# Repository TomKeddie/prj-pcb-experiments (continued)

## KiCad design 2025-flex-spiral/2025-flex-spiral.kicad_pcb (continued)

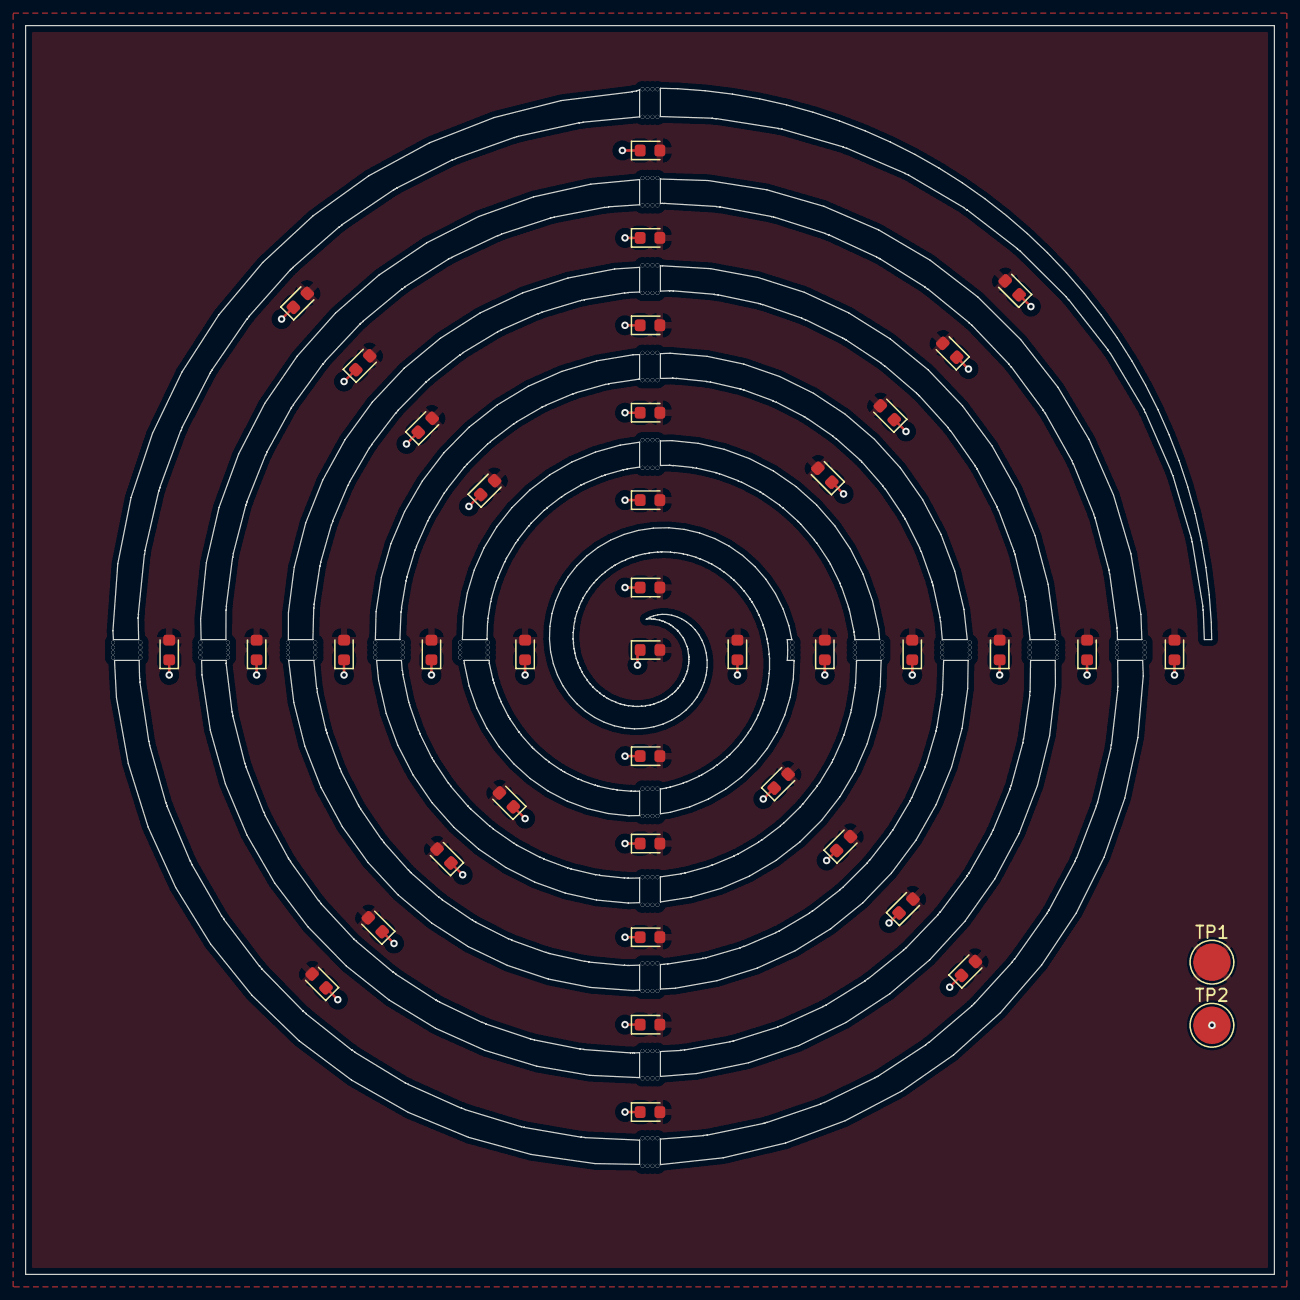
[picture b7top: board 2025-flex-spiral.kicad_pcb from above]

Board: 2 copper layers, 100.0 x 100.0 mm, 41 parts (0 on the bottom side), 2 nets.

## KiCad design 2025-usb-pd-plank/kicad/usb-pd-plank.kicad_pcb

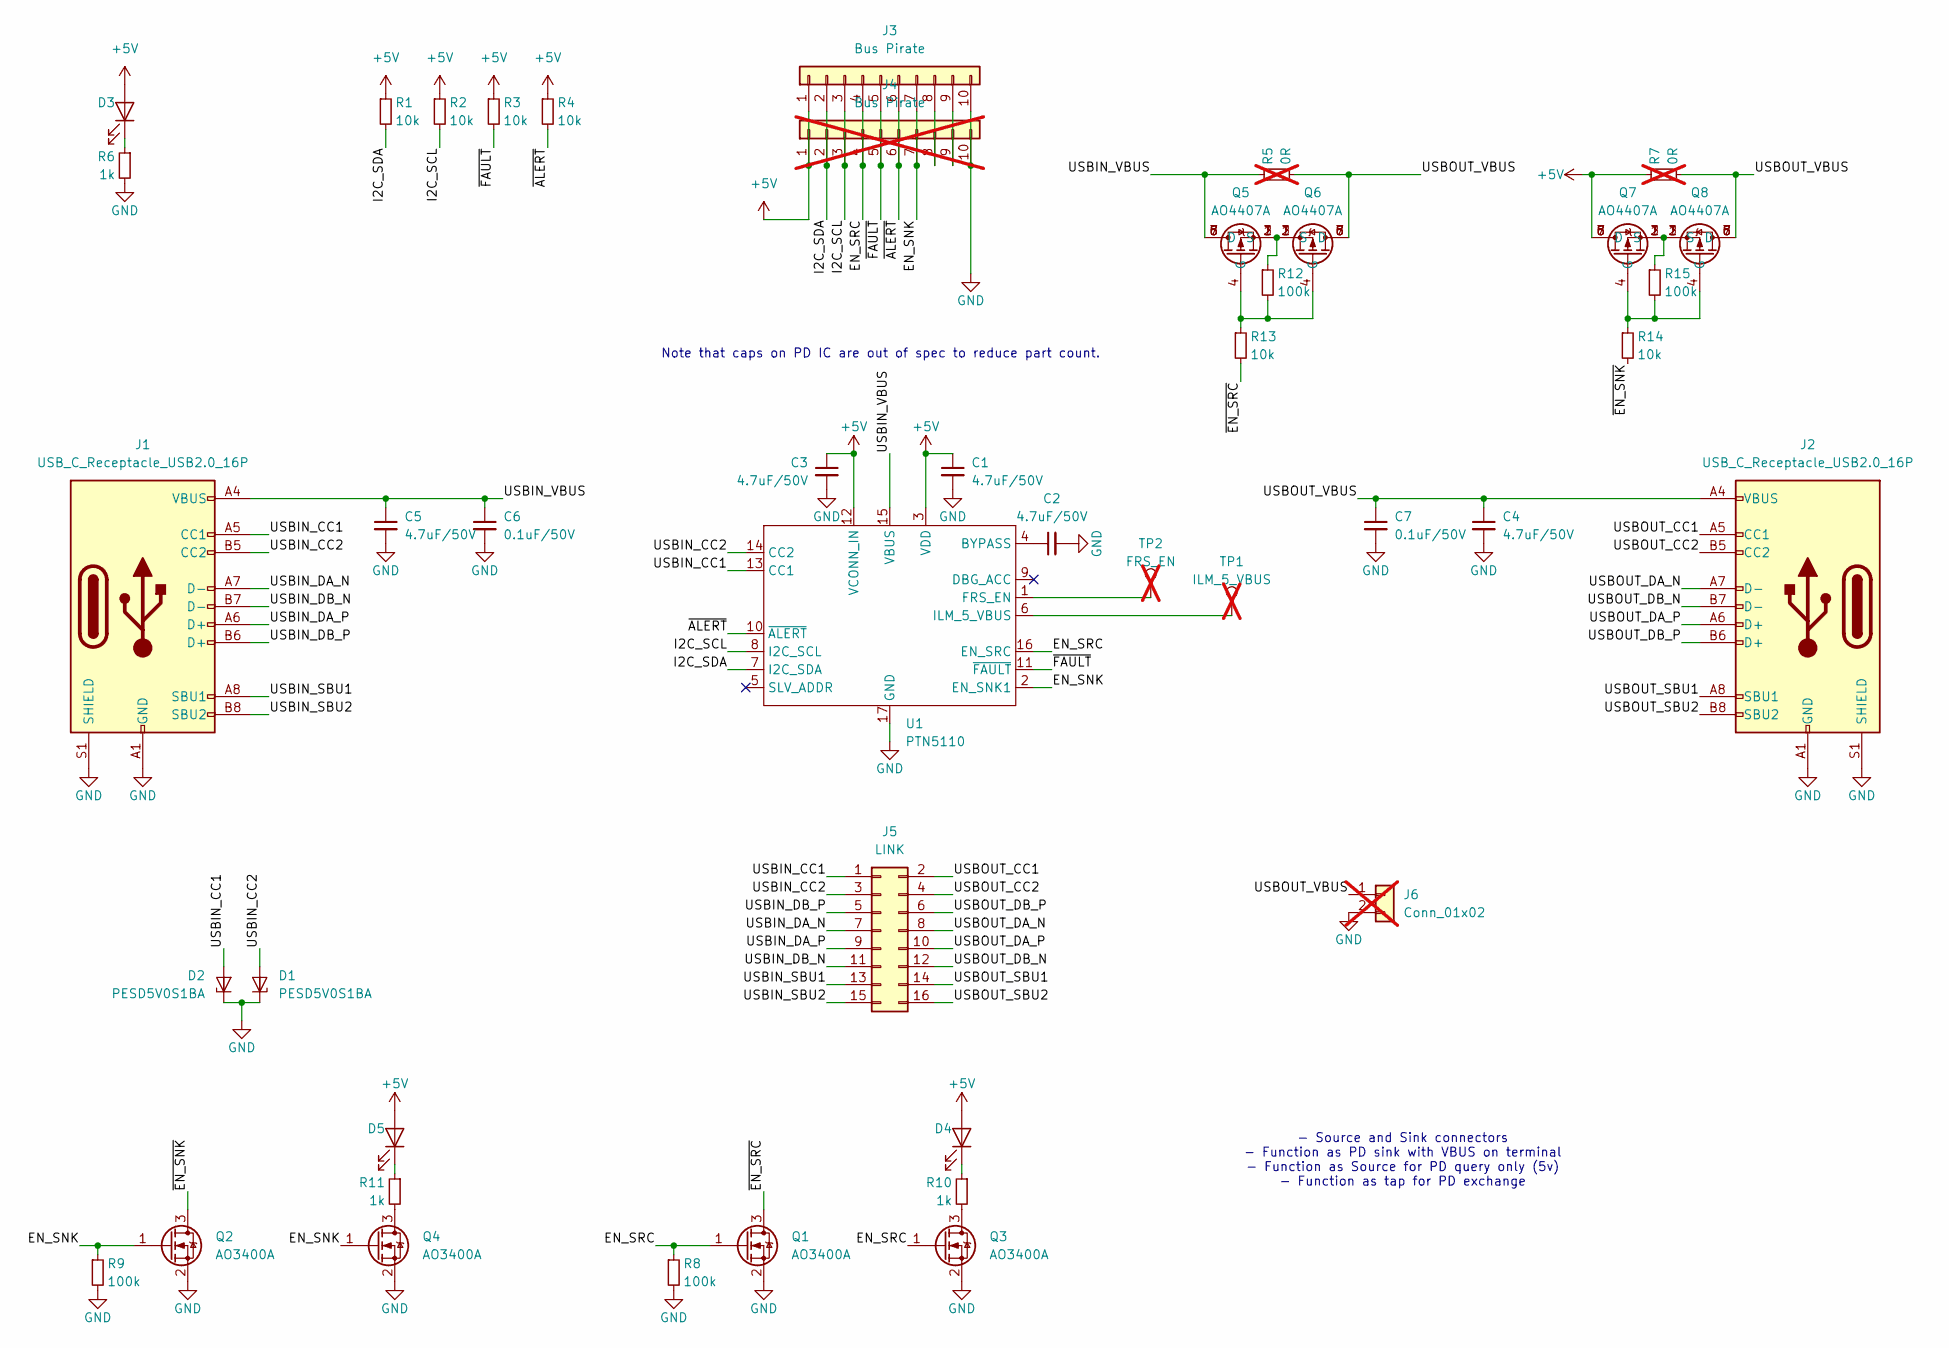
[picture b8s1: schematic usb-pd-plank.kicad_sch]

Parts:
C1, C2, C3, C4, C5: 4.7uF/50V; C_1206_3216Metric; LCSC C29823
C6, C7: 0.1uF/50V; C_1206_3216Metric; LCSC C24497
D1, D2: PESD5V0S1BA; D_SOD-323; LCSC C19224
D3, D4, D5: GREEN; LED_0805_2012Metric; LCSC C2297
J1, J2: USB_C_Receptacle_USB2.0_16P; USB_C_Receptacle_LCSC_C165948; LCSC C165948
J3: Bus Pirate; PinSocket_1x10_P2.54mm_Horizontal
J4: Bus Pirate; PinSocket_1x10_P2.54mm_Vertical; not fitted
J5: LINK; PinHeader_2x08_P2.54mm_Vertical
J6: Conn_01x02; JST_PH_S2B-PH-SM4-TB_1x02-1MP_P2.00mm_Horizontal; not fitted
Q1, Q2, Q3, Q4: AO3400A; SOT-23-GSD; LCSC C20917
Q5, Q6, Q7, Q8: AO4407A; SO-8_3.9x4.9mm_P1.27mm
R1, R2, R3, R4, R13, R14: 10k; R_0402_1005Metric; LCSC C25744
R5, R7: 0R; R_0402_1005Metric; LCSC C17168; not fitted
R6, R10, R11: 1k; R_0402_1005Metric; MFGPN 0402WGF1001TCE; LCSC C11702
R8, R9, R12, R15: 100k; R_0402_1005Metric; MFGPN 0402WGF1003TCE; LCSC C25741
TP1: ILM_5_VBUS; TestPoint_Pad_D1.5mm; not fitted
TP2: FRS_EN; TestPoint_Pad_D1.5mm; not fitted
U1: PTN5110; QFN-16_EP_2.6x2.6_Pitch0.4mm; LCSC C2674062

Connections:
+5V: C1.1, C3.1, D3.2 (A), D4.2 (A), D5.2 (A), J3.1, J4.1, Q7.5 (D), Q7.6 (D), Q7.7 (D), Q7.8 (D), R1.1, R2.1, R3.1, R4.1, R7.1, U1.3 (VDD), U1.12 (VCONN_IN)
/EN_SNK: J3.7, J4.7, Q2.1 (G), Q4.1 (G), R9.1, U1.2 (EN_SNK1)
/EN_SRC: J3.4, J4.4, Q1.1 (G), Q3.1 (G), R8.1, U1.16 (EN_SRC)
/I2C_SCL: J3.3, J4.3, R2.2, U1.8 (I2C_SCL)
/I2C_SDA: J3.2, J4.2, R1.2, U1.7 (I2C_SDA)
/USBIN_CC1: D2.2 (A), J1.A5 (CC1), J5.1, U1.13 (CC1)
/USBIN_CC2: D1.2 (A), J1.B5 (CC2), J5.3, U1.14 (CC2)
/USBIN_DA_N: J1.A7 (D-), J5.7
/USBIN_DA_P: J1.A6 (D+), J5.9
/USBIN_DB_N: J1.B7 (D-), J5.11
/USBIN_DB_P: J1.B6 (D+), J5.5
/USBIN_SBU1: J1.A8 (SBU1), J5.13
/USBIN_SBU2: J1.B8 (SBU2), J5.15
/USBIN_VBUS: C5.1, C6.1, J1.A4 (VBUS), J1.A9 (VBUS), J1.B4 (VBUS), J1.B9 (VBUS), Q5.5 (D), Q5.6 (D), Q5.7 (D), Q5.8 (D), R5.1, U1.15 (VBUS)
/USBOUT_CC1: J2.A5 (CC1), J5.2
/USBOUT_CC2: J2.B5 (CC2), J5.4
/USBOUT_DA_N: J2.A7 (D-), J5.8
/USBOUT_DA_P: J2.A6 (D+), J5.10
/USBOUT_DB_N: J2.B7 (D-), J5.12
/USBOUT_DB_P: J2.B6 (D+), J5.6
/USBOUT_SBU1: J2.A8 (SBU1), J5.14
/USBOUT_SBU2: J2.B8 (SBU2), J5.16
/USBOUT_VBUS: C4.1, C7.1, J2.A4 (VBUS), J2.A9 (VBUS), J2.B4 (VBUS), J2.B9 (VBUS), J6.1, Q6.5 (D), Q6.6 (D), Q6.7 (D), Q6.8 (D), Q8.5 (D), Q8.6 (D), Q8.7 (D), Q8.8 (D), R5.2, R7.2
/~ALERT: J3.6, J4.6, R4.2, U1.10 (~ALERT)
/~EN_SNK: Q2.3 (D), R14.2
/~EN_SRC: Q1.3 (D), R13.2
/~FAULT: J3.5, J4.5, R3.2, U1.11 (~FAULT)
GND: C1.2, C2.2, C3.2, C4.2, C5.2, C6.2, C7.2, D1.1 (K1), D2.1 (K1), J1.A1 (GND), J1.A12 (GND), J1.B1 (GND), J1.B12 (GND), J1.S1 (SHIELD), J2.A1 (GND), J2.A12 (GND), J2.B1 (GND), J2.B12 (GND), J2.S1 (SHIELD), J3.10, J4.10, J6.2, Q1.2 (S), Q2.2 (S), Q3.2 (S), Q4.2 (S), R6.2, R8.2, R9.2, U1.17 (GND)
unnamed: D3.1 (K), R6.1
unnamed: D4.1 (K), R10.1
unnamed: D5.1 (K), R11.1
unnamed: J3.8, J4.8
unnamed: J3.9, J4.9
unnamed: Q3.3 (D), R10.2
unnamed: Q4.3 (D), R11.2
unnamed: Q5.4 (G), Q6.4 (G), R12.2, R13.1
unnamed: Q5.1 (S), Q5.2 (S), Q5.3 (S), Q6.1 (S), Q6.2 (S), Q6.3 (S), R12.1
unnamed: Q7.4 (G), Q8.4 (G), R14.1, R15.2
unnamed: Q7.1 (S), Q7.2 (S), Q7.3 (S), Q8.1 (S), Q8.2 (S), Q8.3 (S), R15.1
unnamed: C2.1, U1.4 (BYPASS)
unnamed: TP2.1, U1.1 (FRS_EN)
unnamed: TP1.1, U1.6 (ILM_5_VBUS)

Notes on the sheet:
Note that caps on PD IC are out of spec to reduce part count.
- Source and Sink connectors - Function as PD sink with VBUS on terminal - Function as Source for PD query only (5v) - Function as tap for PD exchange

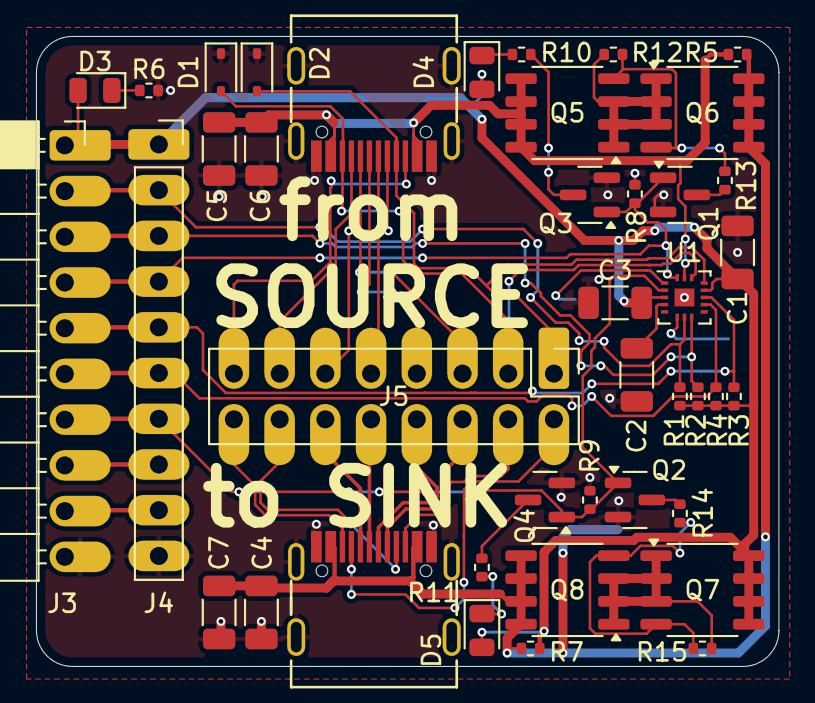
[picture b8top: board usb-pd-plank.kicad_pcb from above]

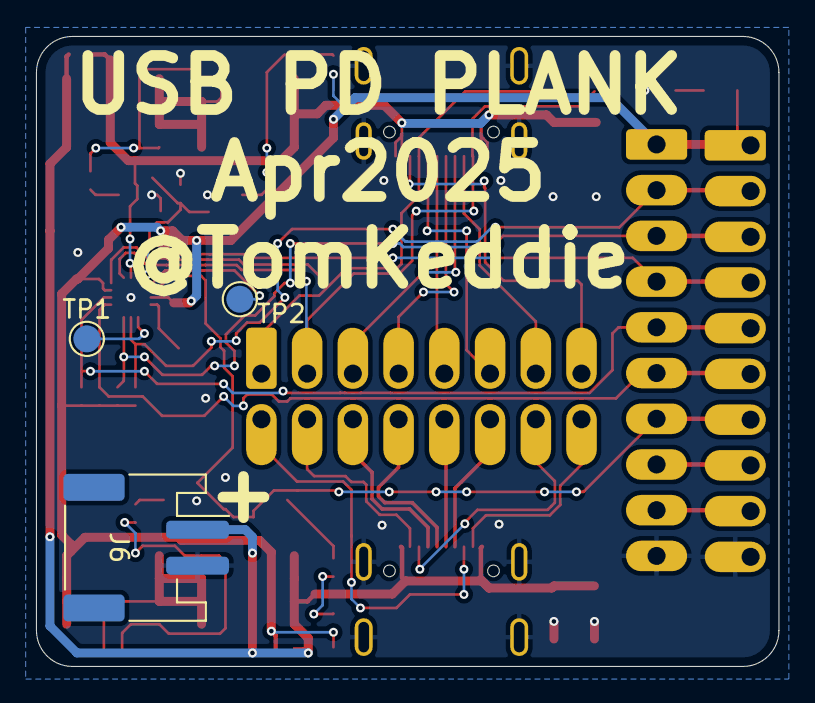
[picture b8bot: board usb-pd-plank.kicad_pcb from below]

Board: 2 copper layers, 41.2 x 35.0 mm, 44 parts (3 on the bottom side), 42 nets.

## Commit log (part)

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2019-01-28 Add led-through-fibreglass test board as submitted to oshpark
2019-08-24 Adding first pass at east van pcb
2019-08-24 Added east-van logo library elements - cu, mask and silk
2019-08-24 Updated east-vanm pcb - add leds - route tracks
2019-08-24 Add remaining east van image files
2019-08-24 East Van pcb as submitted
2019-08-28 Move east van cross to subdirectory
2019-08-28 Add east van arrow image experiments
2019-08-28 Add east van sao outline prototypes
2019-11-01 east-van/pendant-rear: new pcb, swap copper layers
2019-11-01 east-van/pendant-rear: flip silk and mask to create rear (with mirrored writing)
2019-11-01 Update tom-kicad libraries
2019-11-01 east-van: add gimp image.xcf with image portions on different layers
2019-11-01 east-van/pendant: add gerbers
2019-11-21 deutsche-bahn-sao: add scaled and edge images, dxf and footprints (scaled to 70%)
2019-11-21 deutsche-bahn-sao: artwork complete, needs LEDs and sao connector
2019-11-21 Update tom-kicad submodule
2019-11-22 deutsche-bahn: v1.0 as submitted
2019-11-22 mrfixit: add graphics
2019-11-22 mrfixit: add inkspace and dxf
2019-11-22 mrfixit: first pass at pcb
2019-11-22 mrfixit: add copper layers
2019-11-22 mrfixit: v1.0 as submitted, hasl copper outline with red mask internal + multimeter led
2019-11-22 east-van-arrow:add all images
2019-11-22 east-van-arrow: added scaled and filled images
2019-11-23 east-van-arrow: v1.0 as submitted
2019-11-23 east-van-arrow: v1.0 revised larger
2019-11-26 mr-fixit: v1.1 edge cuts changes as v1.0 failed audit
2019-11-26 mr-foxot: add v1.1 gerber zip
2019-11-27 glasgow-pmod: add v1.0
2019-11-29 edison-led-3x4-pmod: rev v1.0
2019-11-29 tom-kicad: added footprints for glasgow pmod adapter
2019-12-07 eat-van-arrow: v1.1 fix issues with back solder mask
2019-12-13 Added various pcb images
2020-01-29 hc245t-bypass: first pass
2020-02-02 hub75-pmod: feb 2020 added
2020-02-02 hc245t-bypass: create panel of two to account for oshpark min size
2020-02-29 hc245t-bypass: Feb 2020 version, increase spacing between boards
2020-02-29 hc245t-bypass: revert to Jan2018 version for flex pcb
2020-02-29 hc245t-bypass : flex version as submitted to oshpark for Feb 2020
2020-03-01 hc245t-bypass: Mar2020 rev with 4 instances
2020-03-01 hc245t-bypass.kicad_pcb: fix solder mask settings
2020-03-02 pi4-pcie-patch: no castellations
2020-03-02 pi4-pcie-patch: add castellations
2020-03-02 pi4-pcie-patch: mask pads on bottom layer
2020-04-09 hub75-pmod: fix issues with oval pads for hub75 connector
2020-04-10 Add covid mask images
2020-04-10 Update gitignore and tom-kicad anchor
2020-04-10 covid-mask: final dxf and jpeg
2020-04-11 covid-mask: add mask2 gerbers
2020-05-18 Glasgow LVDS-PMOD: May 2020 update, fixed mechanical issues
2020-05-24 glasgow-pmod : use relative paths for footprints
2020-05-24 glasgow pmod : fix library references
2020-05-26 glasgow-pmod: tuned J3 and J4 J3_J4_DP1.0/1.0 -> MEETS INTER-PAIR TOLERANCE 1.0000 mm (current delta 0.8724) /Z0 meets intra-pair tolerance 1.0000 mm (current delta 0.0000) /Z1 meets intra-pair toler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
2020-05-31 glasgow pmod: June 2020 release, fix length matching of pairs
2020-06-28 Glasgow lvds pmod - June 2020
2020-07-25 big-clive: add coaster and keytag pcbs
2020-07-25 big-clive: fix zip file naming
2020-08-06 usb3-loopback: new project
2020-08-09 usb-crossover: new pcb to cross HS tx & rx pairs for usb3<->pcie
2020-09-18 add multi-way-usb sep2020a as resent to jlcpcb
2020-09-19 multi-way-usb: fix drc errors related to keepout regions
2020-09-19 update tom-kicad anchor
2020-09-19 multi-way-usb: as submitted
2020-09-20 esp8266-iot: as submitted to jlcpcb
2020-09-29 sao-wall : as sent to jlcpcb Sep 2020
2020-09-29 Update modules
2020-10-10 Add 3rdparty-gerbers
2020-10-10 Submodule updates
2020-10-10 Moved sao-wall to git@github.com:TomKeddie/prj-sao-wall.git
2020-10-14 multi-way-usb: Changed footprint for inverted connectors
2020-10-20 Add p-bjt-spice: pnp spice simulation
2020-10-20 Add p-fet-spice: P channel fet simulation
2020-11-27 multi-way-usb: fix mechanical issues
2020-11-27 Add syzygy-serdes-breakout
2020-11-29 Add atmelice-swd-breakout
2020-11-29 multi-way-usb: move J8 to X2 to balance supplies, v1.2 ready for production
2020-12-08 2021-xmas-tree: add png for ornament
2020-12-10 Add 2021-xmas-tree pcb ornament
2020-12-11 2021-xmas-tree: Dec2020 release
2020-12-11 Add rgb-xmas-tree (need to solve current consumption)
2020-12-11 2021-xmas-tree-2020Dec: reduced to 100mm size to save $$
2020-12-11 atmelice-swd-breakout: Nov2020 release
2020-12-11 Add syzygy-stencil
2020-12-12 syzygy-serdes-breakout: fix missing ground pour on In1
2020-12-12 Add Iron Man gerbers
2020-12-12 peace-sign: add image
2020-12-13 peace-sign-sao: new design
2020-12-16 blue-pill-bmp: add 2.54mm SWD connector
2020-12-16 peace-sign: commit missing updates
2020-12-16 peace-sign-sao: change SAO connector back to 6 pin for stability
2020-12-17 atmelice-swd-breakout-switch: new design
2020-12-28 kicad-symbols-footprints-workshop: pcb workshop files
2021-01-04 Add power blower
2021-01-04 cleanup
2021-01-07 peace-sign-sao: add source image
2021-01-13 kindcalmsafe: new design
2021-01-13 kindcalmsafe: commit unsaved schematic changes
2021-01-15 snoopy-sao: new design
2021-01-15 snoopy-sao: fix silk
2021-01-15 kindcalmsafe: fix 1204 led package
2021-02-04 micromod-carrier: first commit before hub part # change
2021-02-19 esp8266-wiz550io: new design
2021-02-19 esp8266-wiz550io: add gerbers
2021-02-19 esp8266-wiz550io: switch GPIO2 and GPIO4
2021-02-26 atmelice-swd-breakout-switch: add AVR connector (2021Jan rev)
2021-02-26 nrf52dk-trace-pmod: flip data pin orientation to match pmod
2021-02-26 blue-pill-bmp: as submitted
2021-02-26 peace-sign-sao: as submitted
2021-02-26 kindcalmsafe: dxf export
2021-02-26 snoopy-sao/woodstock: first pass on woodstock
2021-02-26 micromod-carrier: progress commit
2021-02-26 esp8266-iot: add comments
2021-02-26 tom-kicad: update anchor
2021-02-26 kicad-symbols-footprints-workshop: add alias
2021-02-26 power-blower: as committed
2021-02-26 reinstate tom-kicad after conflict mess
2021-03-26 galep4-plcc-28: new design
2021-03-27 galep4-plcc-28: Mar2021 release
2021-04-17 esp8266-wiz550io: add kibot output for Feb2021 release
2021-04-19 ft4232h-breakout: Apr2021 release
2021-04-25 keypad-base: new design
2021-04-25 keypad-base: reduced to 6 keys, add mode change side buttons
2021-04-25 keypad-base: Apr2021 release
2021-04-25 keypad-frame: Apr2021 release of keypad frame
2021-04-25 keypad-base: fix silk, add missing edge cuts layer
2021-04-25 ft4232h-breakout: regenerate Apr2021 with edge cuts
2021-04-26 esp8266-wiz550io: regenerate Feb2021 gerbers with missing edge cuts fixed
2021-04-26 keypad-base/keypad-frame: change to M2 standoffs, Apr2021a release
2021-05-30 ft4232h-breakout: may release - change to SMTSO-M3 standoff
2021-05-30 keypad-frame: May2021 release, change to m3 holes, shrink keyswitch cutouts
2021-06-06 ft4232h-breakout: Jun2021 release, fix diameter of spacer
2021-06-06 ft4232h-breakout: Jun2021a release, add power led
2021-06-06 ft4232h-breakout: Jun2021b add silk to voltage selection
2021-06-06 keypad-base: Jun2021 - change standoff type
2021-12-26 micromod-pmod-function: adapter for micromod function to pmod
2022-01-22 keypad-prototype: moved to git@github.com:TomKeddie/prj-keypad-six.git
2022-01-22 usb-c-power-toggle: new design, as sent to Oshpark
2022-02-06 rc2014-compat-backplane: new design feb2022 rev
2022-02-06 rc2014-compat-backplane: remove extra drill files
2022-05-12 ft4232h-breakout: directory restructure to make way for v2.x
2022-05-12 ft4232h-breakout: add v2.x
2022-05-13 ft4232h-breakout: first pass at v3, pcb outline done
2022-05-14 ft4232h-breakout: v3 schematic complete and reviewed
2022-05-15 ft4232h-breakout: v3 at rc1
2022-05-15 ft4232h-breakout: v3.0 as submitted to jlcpcb for pcb run
2022-06-03 ft4232h-breakout: updates for v3.1
    - fixed mount hole sizes
    - fixed exterior dimensions
    - updated rev on silk
2022-12-02 ch348_octo_serial: 8 port usb serial adapter. Placed.
2022-12-03 ch348_octo_serial: fully routed, silk pending
2022-12-04 ch348_octo_serial: Dec2022 as submitted
2022-12-12 2022-xmas-ball: as submitted to jlcpcb/elecrow
2022-12-15 ch348_octo_serial: add pin 1 marking
2022-12-25 covid-dude: SAO based on teachmepcb image, Dec2022 release
2022-12-25 covid-dude: fix date in filename
2023-01-22 ch348_octo_serial_minim: compact ch348 board, wip
2023-01-23 ch348_octo_serial_minim: jan2023 rev ready for production
2023-01-23 ch348_octo_serial_minim: add cover plate pcb
2023-01-23 ch348_octo_serial_minim: move plate to subdir, add cts/rts link, Jan2023a
2023-01-25 covid-dude: add JLCJLC text
2023-03-31 skull-roses: skull and roses game with pcbs
2023-03-31 skull-roses: update Makefile to be generic
2023-03-31 roses: added step file generation
2023-04-20 esp8266-plugpack - new design
2023-04-22 esp8266-plugpack: placed and routed
2023-04-22 esp8266-plugpack: regenerate mfg output
2023-04-24 esp8266-plugpack: Apr2023 release
2023-05-04 atmelice-swd-breakout-switch: fix ground issue, May2023 release
2023-09-13 baggage-label: new design
2023-09-19 webcam-shim: new design
2023-09-23 baggage-label-small: new design
2023-11-01 baggage-label: add mid size and gerbers/Makefile for all
2023-11-18 strange-parts: new coaster design
2023-11-18 strange parts coaster: fix back silk
2023-11-19 strange parts sao: new design
2023-11-19 baggage label: updates
2023-12-21 2023-xmas-snowflake: new design
2024-03-02 mikrobus-pmod: change to 16 poin connector
2024-05-15 2024-businesscard new pcb
2024-06-07 2024-trace-adapter: new design sent to oshpark
2024-09-11 2024-rfid-sao: new design for supercon 2024
2024-09-11 2024-rfid-sao: Update README.md
2024-09-11 2024-rfid-sao: first pass
2024-09-11 2024-rfid-sao: updates for jlcpcb
2024-09-16 mrfixit: rev1.3 as sent for mfg
2024-09-17 2024-trace-adapter: remove lock file ;-)
2024-09-25 2024-syzygy-dsi: add pi schematic
2024-09-25 2024-syzygy-dsi: ready to fab
2024-10-03 2024-rfid-sao:remove from silk circle from antenna
2024-11-12 2024-supercon-sign-sao: new design
    ready for submission to JLC
2024-11-13 2024-supercon-sign-sao: add bottom silk
2024-11-16 2024-rfid-sao: ready for second run
2024-11-16 2024-supercon-sign-sao: restructure ready for software
2024-11-16 2024-supercon-sign-sao: add software
2024-11-20 2024-rfid-sao: change RFID chip to 4k version
2024-11-21 2024-rfid-sao: add location for barcode
2024-12-02 2024-clock-retrofit: first pass at board outline
2024-12-02 2024-rfid-sao: add markdown bom
2024-12-02 2024-rfid-sao: markdown improvements
2024-12-04 2024-clock-retrofit: all leds placed
2024-12-10 2024-clock-retrofit: ready for jlcpcb
2024-12-10 2024-clock-retrofit: fix rotation to match jlc
2024-12-14 baggage-label: add blank
2024-12-15 2024-led-ctrl-24v: progress checkin
2024-12-31 led-ctrl-24v: progress checkin
2025-01-01 2024-led-ctrl-24v: add BUTTONS graphics
2025-04-05 baggage-label: reorganise
2025-04-12 2025-usb-pd-plank: add data sheets
2025-04-17 2025-usb-pd-plank: new design
    Prior to dropping BGA for FETs
2025-04-18 2025-usb-pd-plank: placed and routed
2025-04-19 2025-usb-pd-plank: read for mfg
    Changed i2c resistors to 10k
    Changed all LEDs to green
    Changed all power caps to 4.7uF/50V
    (cost reduction by $us10)
2025-04-20 2025-usb-pd-plank: add VBUS connector, silk fixes. As submitted.
2025-04-27 baggage-label-felix: updates
2025-05-09 2024-clock-retrofit: as submitted April 2025
2025-05-09 2024-led-ctrl-24v: abandoned - too expensive
2025-05-09 2025-usb-pd-plank: fix submission issues
2025-05-30 2025-usb-pd-plank: add 3d render to Makefile
2025-05-30 2025-usb-pd-plank: add iso 3d render to Makefile
2025-06-22 2025-flex-spiral: as submitted
    - no rev on silk
    - forgot to remove JLC batch number from order
2025-06-27 2025-flex-spiral: move first design to one and add design two
2025-07-25 2025-mini-keychain: new design
    2025-06-22-09-39: as submitted
    2025-07-24-13-16: removed silk from front
2025-07-25 2025-usb-pd-plank: 2025-05-29-20-44
2025-08-31 2025-pmod-sma: new design as submitted
